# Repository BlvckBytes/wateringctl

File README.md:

# WateringCtl

A web-based solenoid-valve controller used for watering the garden, plants and the like.

* [Result](#result)
* [Requirements](#requirements)
* [Hardware](#hardware)
  * [usb2serial](#usb2serial)
  * [wifi](#wifi)
  * [relays](#relays)

## Result

## Requirements

* [x] Accomplish all I/O over WiFi
* [x] Long WiFi range to reach the shed
* [x] No external power-supply
* [x] USB connection to debug/upload code
* [x] Sync up multiple UI-clients (websocket event-system)
* [x] Status-LED where blinking-speed indicate system-states
* [x] Control as many valves as needed by having modular boards using shift-registers
* [x] Run a scheduler on-board that can be fully configured
* [x] Switch valves manually
* [x] Store representative string names for each valve
* [x] Disableable intervals, days and valves
* [x] Manually activate valves for a certain duration
* [x] Mobile-friendly web-UI
* [x] Serve the UI from an SD-card
* [x] Manage all files on the SD-card remotely
* [x] Store configurations on the SD-card
* [x] Upload compiled binaries and then flash from SD
* [x] Web SD-file browser
* [ ] Log all debug-relevant information to SD (yyyy-mm-dd_log.txt)
* [ ] Multiple logging levels that can be streamed using a socket endpoint

## Hardware

I use AutoDesk Eagle to design my PCBs, you can find the projects below in `hardware`.

### usb2serial

Converts USB signals to RX, TX, Reset and Programming-Bootmode signals and is used to flash code onto the micro as well as debug through the serial monitor. It's mounted in the project's enclosure and provides a relatively modern port to interface with computers. With this, I can use cheap barebones ESP SoC's without the surrounding arduino-like development board.

### wifi

This board plugs straight into the usb2serial module and represents the most barebones wifi circuit possible. Besides the 3.3V regulation as well as driving an external status-led and the relay-board breakouts, there's not much on there. The antenna is also broken out to an external antenna screw-connector to ensure proper wifi reception.

### relays

This board requires 5VDC to power logic, 12VDC for the relays and 24VAC to control the valves using said relays. The 595 shift-register controls all eight relays through on-board transistors safely, since each relay has it's own reverse diode to catch collapsing field currents. Boards can be chained together to have as many valves as you'd like, since D_IN and D_OUT are exposed separately.

### supply

As a power-supply I'm using a simple buck-/boost-converter which steps down 12V to 5V. The 5V will power the 595 relay board directly where as the ESP board will regulate it down further to it's required 3.3V. The toroid-transformer has two equal 12V secondary windings: I'm using one of them through a full bridge rectifier as well as the converter and then both windings in series for the external valves, as they run on 24VAC.

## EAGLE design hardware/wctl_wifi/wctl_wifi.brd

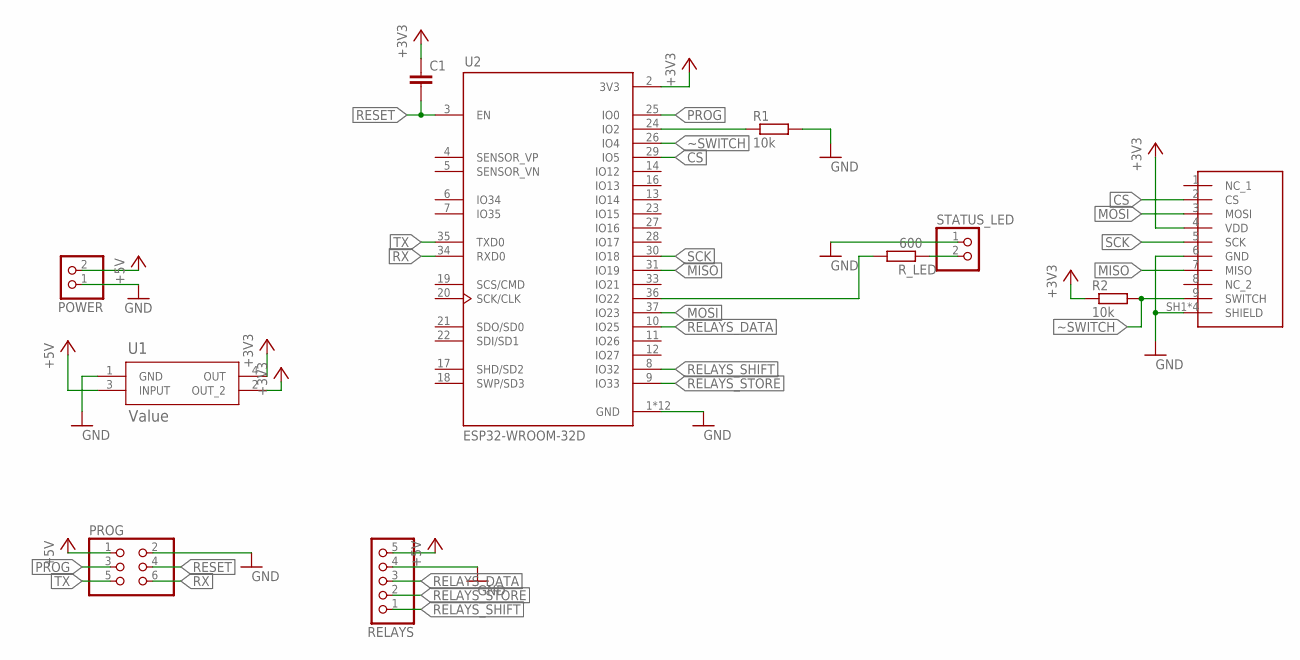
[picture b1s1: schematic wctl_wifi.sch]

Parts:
C1: C-EUC0603; C0603
POWER: PINHD-1X2; 1X02
PROG: PINHD-2X3; 2X03
R1, R2: 10k; R0603
RELAYS: PINHD-1X5; 1X05
R_LED: 600; R0603
STATUS_LED: PINHD-1X2; 1X02
U1: Value; DCY0004A_M
U2: ESP32-WROOM-32D; MODULE_ESP32-WROOM-32D
U$1: SD_SLOT

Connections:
+3V3: C1.1, R2.1, U1.2 (OUT_2), U1.4 (OUT), U2.2 (3V3), U$1.4 (VDD)
+5V: POWER.2, PROG.1, RELAYS.5, U1.3 (INPUT)
CS: U2.29 (IO5), U$1.2 (CS)
GND: POWER.1, PROG.2, R1.2, RELAYS.4, STATUS_LED.1, U1.1 (GND), U2.1 (GND), U2.15 (GND), U2.38 (GND), U2.39_1 (GND), U2.39_2 (GND), U2.39_3 (GND), U2.39_4 (GND), U2.39_5 (GND), U2.39_6 (GND), U2.39_7 (GND), U2.39_8 (GND), U2.39_9 (GND), U$1.6 (GND), U$1.SH1 (SHIELD), U$1.SH2 (SHIELD), U$1.SH3 (SHIELD), U$1.SH4 (SHIELD)
MISO: U2.31 (IO19), U$1.7 (MISO)
MOSI: U2.37 (IO23), U$1.3 (MOSI)
unnamed: R_LED.1, STATUS_LED.2
unnamed: R_LED.2, U2.36 (IO22)
unnamed: R1.1, U2.24 (IO2)
PROG: PROG.3, U2.25 (IO0)
RELAYS_DATA: RELAYS.3, U2.10 (IO25)
RELAYS_SHIFT: RELAYS.1, U2.8 (IO32)
RELAYS_STORE: RELAYS.2, U2.9 (IO33)
RESET: C1.2, PROG.4, U2.3 (EN)
RX: PROG.6, U2.34 (RXD0)
SCK: U2.30 (IO18), U$1.5 (SCK)
TX: PROG.5, U2.35 (TXD0)
~SWITCH: R2.2, U2.26 (IO4), U$1.9 (SWITCH)

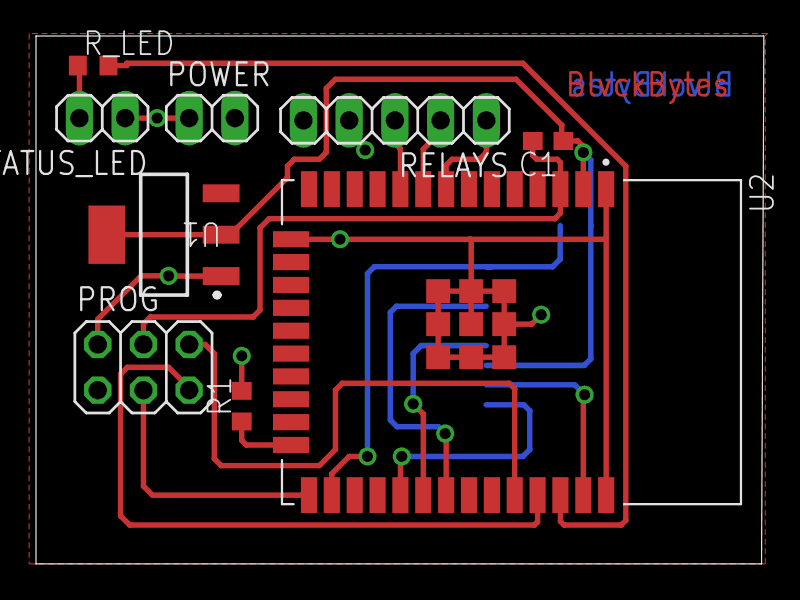
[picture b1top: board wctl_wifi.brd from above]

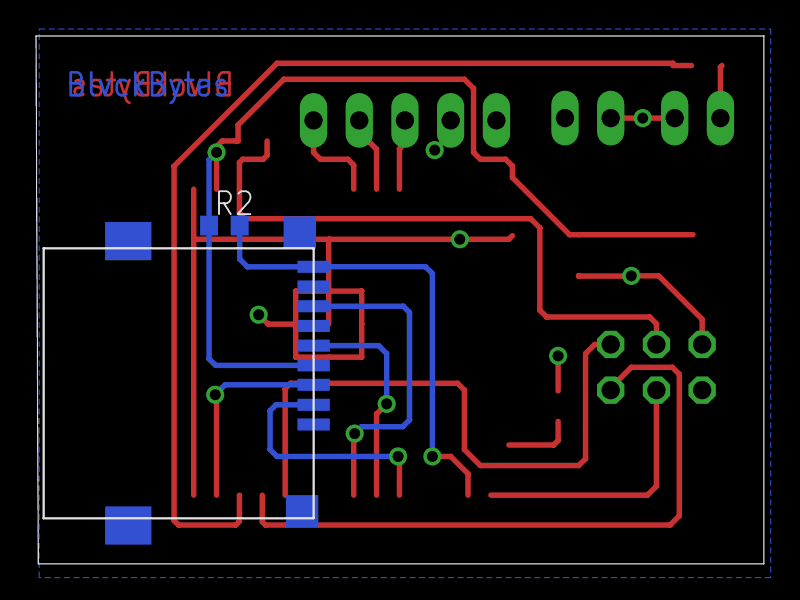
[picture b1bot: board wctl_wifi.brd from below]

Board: 2 copper layers, 40.4 x 29.3 mm, 11 parts (2 on the bottom side), 18 nets.

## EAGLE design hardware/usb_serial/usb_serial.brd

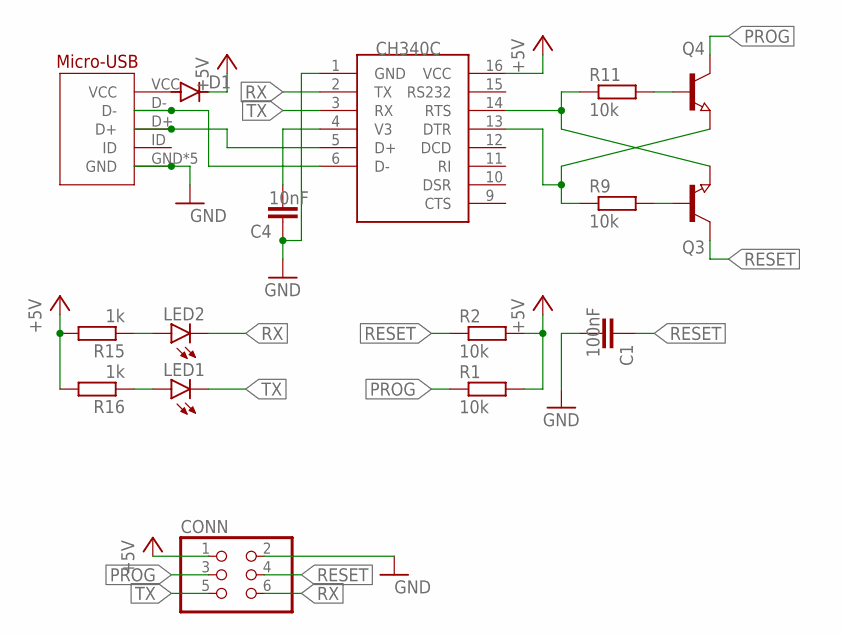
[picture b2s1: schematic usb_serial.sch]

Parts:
C1: 100nF; C0603K
C4: 10nF; C0603K
CONN: PINHD-2X3; 2X03
D1: DIODE-MICROMELF-R; MICROMELF-R
J1: MICRO-USB
LED1, LED2: LEDCHIPLED_0805; CHIPLED_0805
Q3, Q4: NPN-TRANSISTOR_SOT23; SOT23
R1, R2, R9, R11: 10k; R0603
R15, R16: 1k; R0603
U$3: CH340C; SOIC16

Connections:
+5V: CONN.1, D1.C, R1.2, R2.2, R15.2, R16.2, U$3.16 (VCC)
DTR: Q4.2 (E), R9.1, U$3.13 (DTR)
GND: C1.2, C4.1, CONN.2, J1.GND, J1.GP1 (GND), J1.GP2 (GND), J1.GP3 (GND), J1.GP4 (GND), U$3.1 (GND)
unnamed: D1.A, J1.VCC
unnamed: C4.2, U$3.4 (V3)
unnamed: J1.D+, U$3.5 (D+)
unnamed: J1.D-, U$3.6 (D-)
unnamed: Q3.1 (B), R9.2
unnamed: Q4.1 (B), R11.2
unnamed: LED1.A, R16.1
unnamed: LED2.A, R15.1
PROG: CONN.3, Q4.3 (C), R1.1
RESET: C1.1, CONN.4, Q3.3 (C), R2.1
RTS: Q3.2 (E), R11.1, U$3.14 (RTS)
RX: CONN.6, LED2.C, U$3.2 (TX)
TX: CONN.5, LED1.C, U$3.3 (RX)

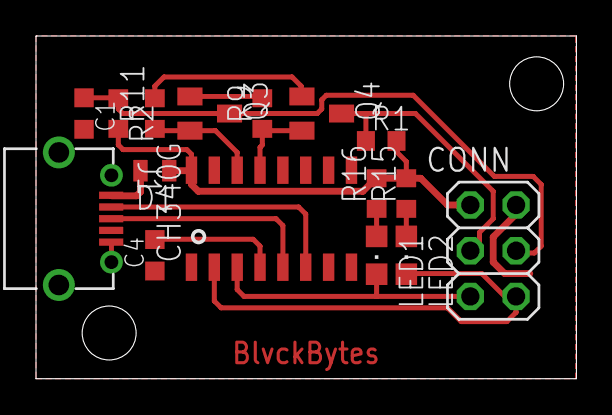
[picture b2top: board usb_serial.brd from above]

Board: 2 copper layers, 30.0 x 19.0 mm, 16 parts (0 on the bottom side), 16 nets.

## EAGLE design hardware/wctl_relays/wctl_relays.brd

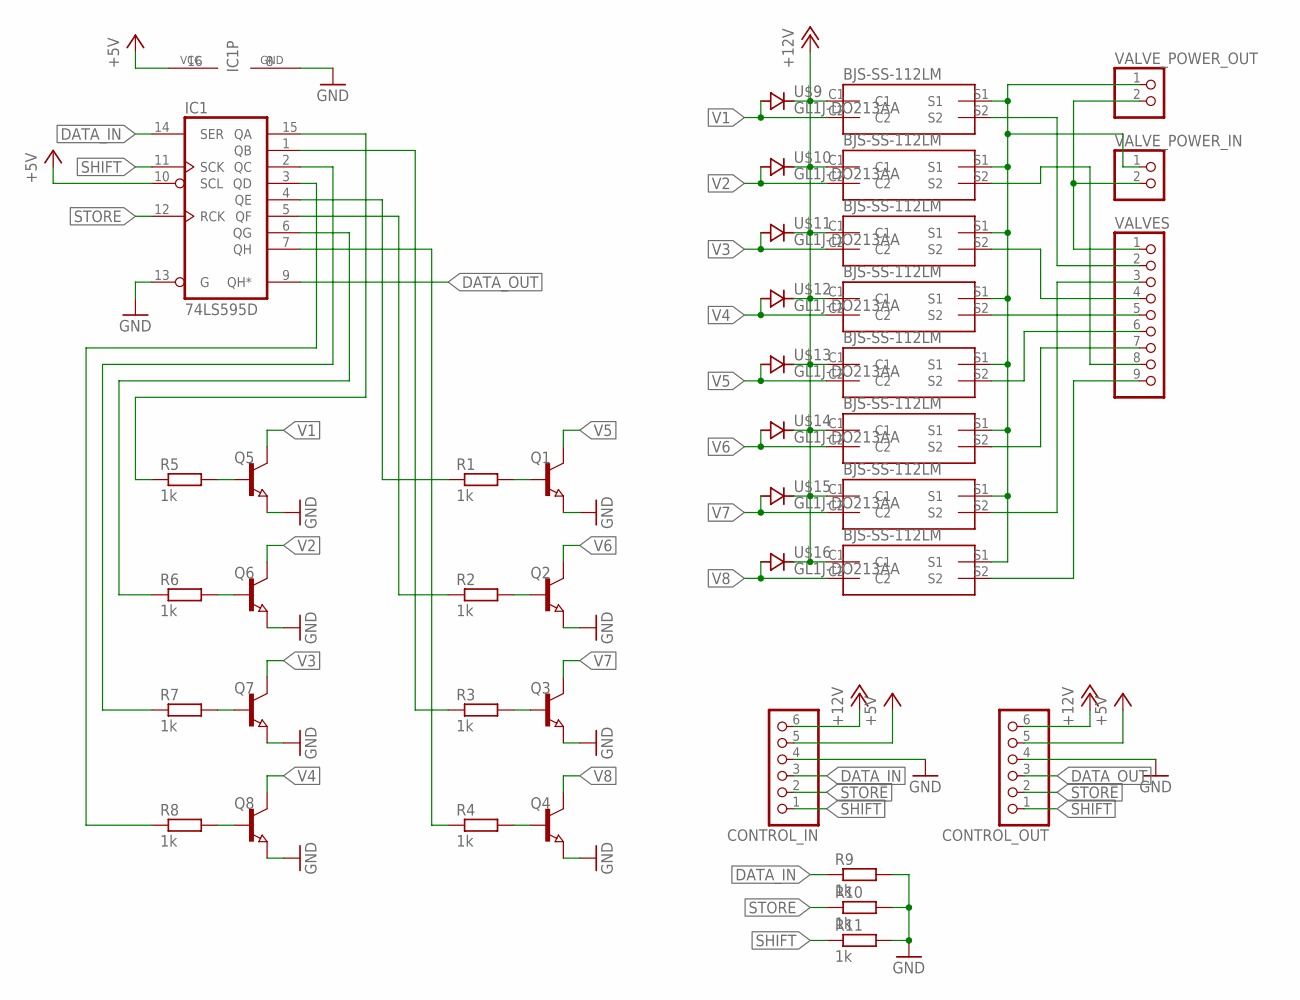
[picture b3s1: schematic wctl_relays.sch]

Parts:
CONTROL_IN: PINHD-1X6; 1X06
CONTROL_OUT: PINHD-1X6; 1X06
IC1: 74LS595D; SO16
Q1, Q2, Q3, Q4, Q5, Q6, Q7, Q8: NPN-TRANSISTOR_SOT23; SOT23
R1, R2, R3, R4, R5, R6, R7, R8, R9, R10, R11: 1k; R0603
U$1, U$2, U$3, U$4, U$5, U$6, U$7, U$8: BJS-SS-112LM
U$9, U$10, U$11, U$12, U$13, U$14, U$15, U$16: GL1J-DO213AA
VALVES: PINHD-1X9; 1X09
VALVE_POWER_IN: PINHD-1X2; 1X02
VALVE_POWER_OUT: PINHD-1X2; 1X02

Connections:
+5V: CONTROL_IN.5, CONTROL_OUT.5, IC1.10 (SCL), IC1.16 (VCC)
+12V: CONTROL_IN.6, CONTROL_OUT.6, U$1.C1, U$2.C1, U$3.C1, U$4.C1, U$5.C1, U$6.C1, U$7.C1, U$8.C1, U$9.C, U$10.C, U$11.C, U$12.C, U$13.C, U$14.C, U$15.C, U$16.C
DATA_IN: CONTROL_IN.3, IC1.14 (SER), R9.1
DATA_OUT: CONTROL_OUT.3, IC1.9 (QH*)
GND: CONTROL_IN.4, CONTROL_OUT.4, IC1.8 (GND), IC1.13 (G), Q1.2 (E), Q2.2 (E), Q3.2 (E), Q4.2 (E), Q5.2 (E), Q6.2 (E), Q7.2 (E), Q8.2 (E), R9.2, R10.2, R11.2
unnamed: U$2.S2, VALVES.8
unnamed: U$4.S2, VALVES.5
unnamed: U$5.S2, VALVES.6
unnamed: U$6.S2, VALVES.7
unnamed: U$7.S2, VALVES.3
unnamed: U$8.S2, VALVES.9
unnamed: U$3.S2, VALVES.4
unnamed: U$1.S2, VALVES.2
unnamed: VALVES.1, VALVE_POWER_IN.2, VALVE_POWER_OUT.2
unnamed: Q1.1 (B), R1.2
unnamed: Q2.1 (B), R2.2
unnamed: Q3.1 (B), R3.2
unnamed: Q4.1 (B), R4.2
unnamed: Q5.1 (B), R5.2
unnamed: Q6.1 (B), R6.2
unnamed: Q7.1 (B), R7.2
unnamed: Q8.1 (B), R8.2
unnamed: IC1.15 (QA), R5.1
unnamed: IC1.6 (QG), R6.1
unnamed: IC1.2 (QC), R7.1
unnamed: IC1.3 (QD), R8.1
unnamed: IC1.4 (QE), R1.1
unnamed: IC1.5 (QF), R2.1
unnamed: IC1.1 (QB), R3.1
unnamed: IC1.7 (QH), R4.1
unnamed: U$1.S1, U$2.S1, U$3.S1, U$4.S1, U$5.S1, U$6.S1, U$7.S1, U$8.S1, VALVE_POWER_IN.1, VALVE_POWER_OUT.1
SHIFT: CONTROL_IN.1, CONTROL_OUT.1, IC1.11 (SCK), R11.1
STORE: CONTROL_IN.2, CONTROL_OUT.2, IC1.12 (RCK), R10.1
V1: Q5.3 (C), U$1.C2, U$9.A
V2: Q6.3 (C), U$2.C2, U$10.A
V3: Q7.3 (C), U$3.C2, U$11.A
V4: Q8.3 (C), U$4.C2, U$12.A
V5: Q1.3 (C), U$5.C2, U$13.A
V6: Q2.3 (C), U$6.C2, U$14.A
V7: Q3.3 (C), U$7.C2, U$15.A
V8: Q4.3 (C), U$8.C2, U$16.A

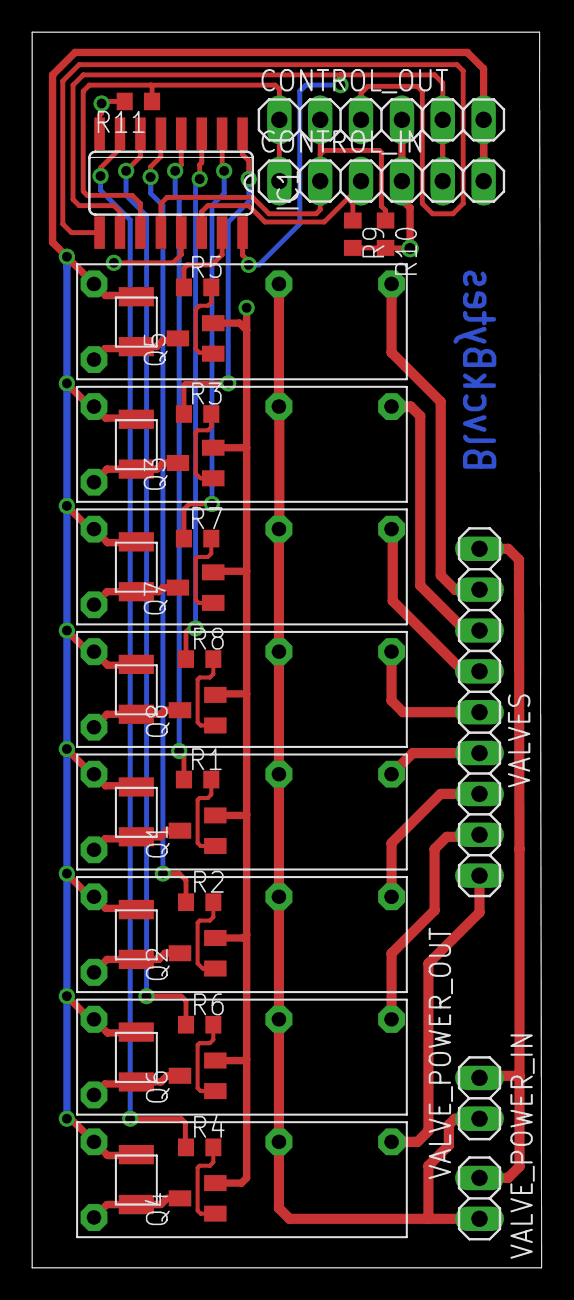
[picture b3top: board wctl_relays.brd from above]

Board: 2 copper layers, 31.7 x 76.8 mm, 41 parts (0 on the bottom side), 41 nets.

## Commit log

2022-02-27 Implemented scheduler
2022-02-27 Added scheduler persistence using EEPROM, implemented schedule printing
2022-02-27 Implemented webserver scaffolding, changed folder structure
2022-02-27 Implemented GET /scheduler endpoint and thus added all needed utilities, started to lay out the API contract
2022-02-28 Worked on the JSON handler (datastructures, setters/inserters and stringification), wrote small a test for it
2022-02-28 Applied the new jsonh to web_server, fixed jsonh non-terminated string issue
2022-02-28 Deleted obsolete file
2022-02-28 Implemented jsonh getters and some very very light testing
2022-02-28 Implemented the scheduler/{day} API route
2022-02-28 Implemented proper 404 response
2022-02-28 Implemented basic json string-value escaping
2022-02-28 Implemented /scheduler/{day}/{index} route
2022-02-28 Implemented body-segment collector
2022-03-01 Implemented jsonh_parse_str, manually tested it, updated service-rest
2022-03-01 Implemented jsonh_parse_num and manually tested it
2022-03-01 Implemented jsonh_parse_literal and manually tested it
2022-03-01 Implemented jsonh_parse_arr and jsonh_parse_obj, completed jsonh_parse, tested with a small example, made adapted dynarr_result_t and htable_result_t to enumlut style
2022-03-01 Added negative number support to the json parser
2022-03-01 Migrated to using libblvckstd, made first use of jsonh_parse as a beautifier echo
2022-03-01 Implemented scheduler_interval_t parsing from json req
2022-03-02 Moved scheduler related jsonifiers into scheduler, cleaned up body preprocessing
2022-03-02 Simplified web_server_str_body_handler
2022-03-03 Cleaned up body handling
2022-03-03 Implemented interval altering and deletion
2022-03-03 Decluttered main by separating out wifi, time_provider and valve_control, improved error handling of those
2022-03-03 Implemented valve alias EEPROM store/load, as well as basic toggle
2022-03-03 Added REST valve edit, turning valves on and off as well as listing all available valves
2022-03-03 Implemented shift register pin control and tied it into valve_control
2022-03-03 Added alias name to event logger
2022-03-03 Changed duplicate log message
2022-03-06 Added hardware project files
2022-03-07 Began working on an interface design, updated readme
2022-03-07 Added another gitignore
2022-03-07 Implemented persistent disabled property on valves
2022-03-07 Implemented persistent disabled property on intervals
2022-03-07 Added missing comments
2022-03-07 Implemented persistent disabled property on days
2022-03-08 Updated readme, added hardware
2022-03-08 Implemented status-led, memstat route and migrated from esp32 to esp07
2022-03-31 Migrated back to ESP32, updated pins in code and updated hardware, also updated readme
2022-03-31 Started to work on the web-ui
2022-03-31 Implemented UI localization
2022-03-31 Partially implemented the UI interval table
2022-03-31 ui: added missing p-tag wraps
2022-03-31 readme: added another requirement
2022-03-31 ui: isolated valve buffer into service
2022-03-31 ui: extracted row-table styles, partially implemented valves table
2022-03-31 ui: added dummy icon buttons; fixed table layouting; further extracted styles
2022-03-31 ui: further refactored sass globals into their own files
2022-04-01 ui: implemented basic column sorting
2022-04-01 ui: implemented notification center
2022-04-01 ui: implemented overlay stack
2022-04-01 ui: implemented textbox, finished valve-alias-edit overlay
2022-04-01 firmware: added error codes, added cors options preflight support
2022-04-01 ui: fully implemented valve alias edit, added error-handler interceptor with status-code translation
2022-04-01 ui: added state persistence, now saving column sort directions
2022-04-01 ui: implemented valve disable toggle; implemented textbox autofocus flag
2022-04-01 firmware: added missing CORS response and added DELETE to the allowed methods
2022-04-01 ui: implemented state toggle
2022-04-01 ui: added small internal todo list
2022-04-01 ui: extracted timespan into it's own component; started working on the overlay for interval-target editing
2022-04-01 ui: implemented textbox typeahead with validation and made use of it in interval target editing; finished interval target editing; fixed various small layoutings
2022-04-01 ui: created vert-range and made use of it in the interval timestamps edit overlay - not quite done yet
2022-04-01 ui: fixed vert range emission issue
2022-04-01 ui: Finished timespan edit overlay
2022-04-01 ui: adjusted vert-range mobile delta-y scale factor; added todo entry
2022-04-01 ui: implemented disable day button
2022-04-01 ui: implemented interval deletion button with confirmation prompt
2022-04-01 ui: implemented interval disable button
2022-04-01 ui: implemented loading indicator
2022-04-01 ui: refined error handling
2022-04-01 ui: fixed body scrolling issue; enlarged language icon; changed order of operations in interceptor
2022-04-01 ui: started working on the valve timer overlay
2022-04-01 ui: fixed loading indicator service change detector issue
2022-04-01 ui: debounced loading indicator
2022-04-01 firmware: implemented basic event system using websockets
2022-04-01 ui: implemented basic web socket handler and started working on the event recognition
2022-04-02 firmware: implemented remaining websocket events
2022-04-02 ui: implemented remaining websocket events
2022-04-02 firmware: started to implement valve timer functionality
2022-04-02 documentation: updated rest description file
2022-04-02 firmware: collapsed valve timer cleared and set events into a single update event
2022-04-02 ui: started implementing valve timer events and functionality
2022-04-02 firmware: now forbidding turning off valves with an active timer
2022-04-02 firmware: renamed field 'timer' to 'duration', as per contract
2022-04-02 ui: implemented all valve-timer related features
2022-04-02 firmware: implemented valve timer decrementing, refactored a bit to avoid a cyclical header include
2022-04-02 documentation: updated readme
2022-04-02 ui: moved file from wrong location into project folder
2022-04-02 firmware: changed valve-related response code
2022-04-02 ui: changed valve-related response code
2022-04-02 ui: removed schedule play button (feature removed)
2022-04-02 ui: changed loading indicator to a static svg
2022-04-02 ui: changed favicon
2022-04-02 firmware: fixed scheduler ref issue, changed utc-offs to be appropriate for my tz
2022-04-02 ui: slowed down vert-range scroll speed on mobile
2022-04-02 firmware: the scheduler now turns off blocked intervals if they're blocked while being active
2022-04-02 ui: fixed websocket connection attempt spam
2022-04-02 firmware: added missing WSE_VALVE_RENAME listener to page-schedules
2022-04-03 firmware: implemented static file serving from SD card; prefixed all API endpoints with /api; changed 404 behavior to always serve angular's index for non /api routes
2022-04-03 ui: altered url building to use the url-bar on non-localhost; fixed scheduler weekday auto-select bug
2022-04-03 firmware: refactored web server routes into their own files
2022-04-03 firmware: worked on the FS endpoints; implemented file read and directory listing; implemented (recursive) file deletion - with a timeout issue to be fixed
2022-04-03 documentation: added FS endpoints to api contract
2022-04-03 firmware: fixed connection hangup crash
2022-04-03 firmware: refactored web-sockets into their own files; translated fs rest API into a websocket API to avoid timeouts
2022-04-03 firmware: simplified body collector
2022-04-03 ui: adapted to new endpoints
2022-04-03 firmware: implemented remaining FS socket endpoint functionality; tested with 500K files, built with larger files in mind
2022-04-04 firmware: generalized task arg struct
2022-04-04 hardware: updated wifi board
2022-04-04 documentation: updated readme to latest hardware; updated requirements
2022-04-04 firmware: moved misplaced delay; gave fs-fetch-task a higher priority
2022-04-04 ui: started working on the file manager
2022-04-04 firmware: implemented file write cancelation on client disconenct
2022-04-04 ui: implemented file listing and directory creation - proper error-handling is yet to be done
2022-04-04 ui: changed file manager layout; added connected observable pipe to ensure only emitting true once; implemented delete
2022-04-04 ui: added timeout functionality to the loading indicator
2022-04-04 ui: added loading indicator to fileman; fixed loading indicator bug
2022-04-04 ui: started to implement file editing; implemented file content fetching; implemented path-bar back button
2022-04-04 firmware: changed file content fetch protocol header
2022-04-04 ui: fixed loading-screen height issue
2022-04-04 ui: added proper path joining
2022-04-04 ui: added delete confirmation notification; made notifications more convenient
2022-04-04 ui: added missing autofocus directive
2022-04-05 ui: implemented proper file editor
2022-04-05 ui: added recipient await to fight race conditions
2022-04-05 firmware: added missing file close; altered file read prio; implemented file overwrite command; added empty packet ignore
2022-04-05 ui: implemented file save after edit
2022-04-05 ui: implemented file creation
2022-04-05 ui: added missing ondestroy hooks for subsink
2022-04-05 ui: added success and error notifications with a central interceptor; added overlay enter key recognition
2022-04-05 firmware: fixed file closed too early to read directory flag
2022-04-05 ui: added component destroy on navigation
2022-04-05 ui: finished file upload implementation
2022-04-06 ui: implemented fully fledged sorted-table; applied said table on the browser-page
2022-04-06 ui: added column-precedence direction as well as external sorting functionality to the sorted-table
2022-04-06 documentation: added another image to the readme
2022-04-06 documentation: forgot to actually commit the image
2022-04-06 firmware: implemented untar command
2022-04-06 ui: implemented untar command
2022-04-07 firmware: refactored untar; added filename guard to detect corrupted TARs
2022-04-07 firmware: implemented untar progress messages; set priority to a more sane value and added a macro for the value
2022-04-07 ui: implemented progress message processing through an interception
2022-04-08 firmware: implemented request queue for async commands - this will combat slow task stack releases as no new tasks are spawned per request now
2022-04-08 ui: added file download capability
2022-04-08 firmware: implemented a better file chunking protocol
2022-04-08 ui: adapted to the new file chunking protocol
2022-04-08 firmware: implemented firmware updating from SD
2022-04-08 ui: added firmware update functionality
2022-04-09 firmware: migrated valve storage from eeprom to sd json
2022-04-09 ui: changed dev port of fileman
2022-04-09 migrated scheduler storage from eeprom to sd json; integrated a few libblvckstd changes
2022-04-09 firmware: migrated valve persistence from json to binary
2022-04-09 firmware: migrated scheduler persistence from json to binary
2022-04-09 firmware: removed obsolete /scheduler endpoint
2022-04-09 documentation: removed obsolete /scheduler endpoint
2022-04-09 ui: fixed bug where created intervals can have unexpected durations
2022-04-09 firmware: incremented maximum number of intervals per day, since the system now supports higher values
2022-04-10 ui: added missing duration constraint
2022-04-16 firmware: added support for meshed networks
2022-04-18 ui: fixed i18n relative path issue when using base-href build flag
2022-04-18 firmware: Increased SD SPI-speed x4, changed the web-root and implemented more sophisticated 404-handling logic

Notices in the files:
parts and their libraries:
COPYRIGHT: Copyright (C) 2018 Accelerated Designs. All rights reserved
